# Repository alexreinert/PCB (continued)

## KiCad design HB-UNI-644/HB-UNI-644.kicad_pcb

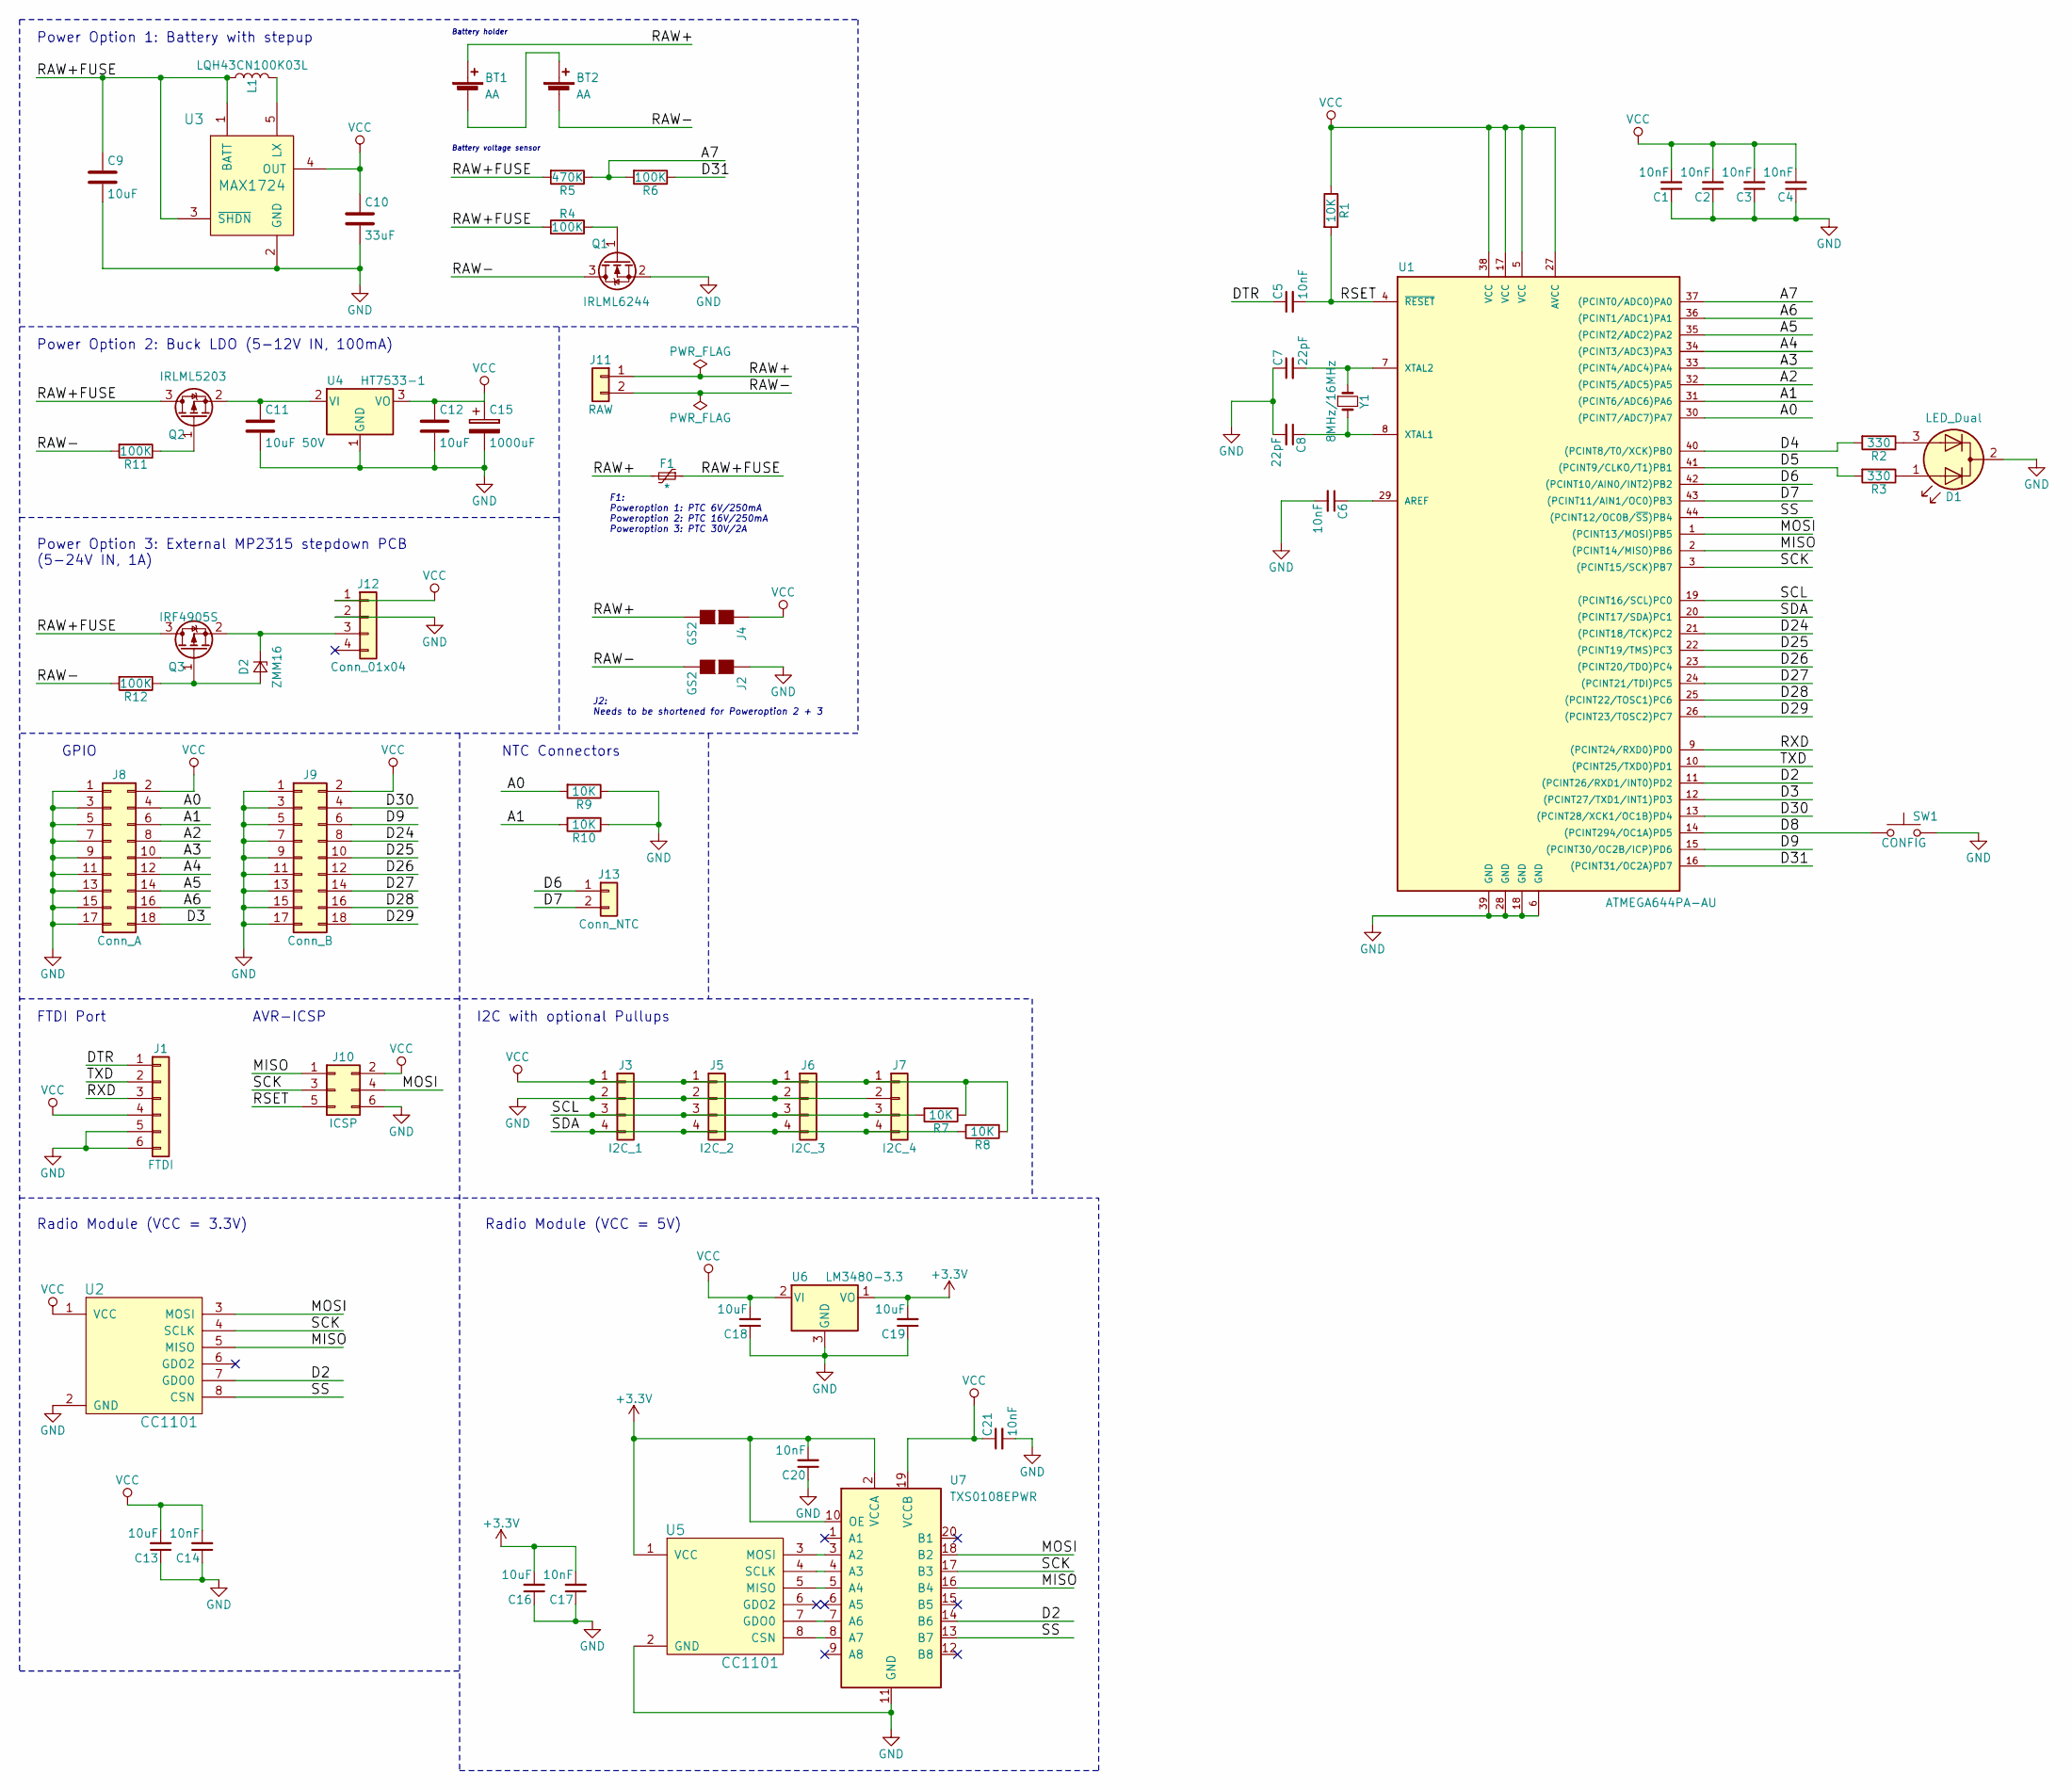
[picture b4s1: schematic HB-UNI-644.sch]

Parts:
BT1, BT2: AA; BATTERY_HOLDER_GOOBAY_AA
C1, C2, C3, C4, C5, C6, C14, C17, C20, C21: 10nF; C_0805_HandSoldering
C7, C8: 22pF; C_0805_HandSoldering
C9, C12, C13, C16, C18, C19: 10uF; C_0805_HandSoldering
C10: 33uF; C_1206_HandSoldering
C11: 10uF 50V; C_1206_HandSoldering
C15: 1000uF; CP_Radial_D8.0mm_P3.50mm
D1: LED_Dual; LED_D3.0mm-3
D2: ZMM16; D_MiniMELF_Handsoldering
F1: *; R_1206_HandSoldering
J1: FTDI; Pin_Header_Straight_1x06_Pitch2.54mm
J2, J4: GS2
J3: I2C_1; Pin_Header_Straight_1x04_Pitch2.54mm
J5: I2C_2; Pin_Header_Straight_1x04_Pitch2.54mm
J6: I2C_3; Pin_Header_Straight_1x04_Pitch2.54mm
J7: I2C_4; Pin_Header_Straight_1x04_Pitch2.54mm
J8: Conn_A; Pin_Header_Straight_2x09_Pitch2.54mm
J9: Conn_B; Pin_Header_Straight_2x09_Pitch2.54mm
J10: ICSP; Pin_Header_Straight_2x03_Pitch2.54mm
J11: RAW; Pin_Header_Straight_1x02_Pitch2.54mm
J12: Conn_01x04; Pin_Header_Straight_1x04_Pitch2.54mm
J13: Conn_NTC; Pin_Header_Straight_2x01_Pitch2.54mm
L1: LQH43CN100K03L; L_1812_HandSoldering
Q1: IRLML6244; SOT-23_Handsoldering
Q2: IRLML5203; SOT-23_Handsoldering
Q3: IRF4905S; TO-263-2
R1, R7, R8, R9, R10: 10K; R_0805_HandSoldering
R2, R3: 330; R_0805_HandSoldering
R4, R6, R11, R12: 100K; R_0805_HandSoldering
R5: 470K; R_0805_HandSoldering
SW1: CONFIG; SW_SPST_FSMSM
U1: ATMEGA644PA-AU; TQFP-44_10x10mm_Pitch0.8mm
U2, U5: CC1101
U3: MAX1724; TSOT-23-5_HandSoldering
U4: HT7533-1; SOT-89-3_Handsoldering
U6: LM3480-3.3; SOT-23
U7: TXS0108EPWR; TSSOP-20_4.4x6.5mm_Pitch0.65mm
Y1: 8MHz/16MHz; Crystal_HC49-U_Vertical

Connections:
+3V3: C16.2, C17.2, C19.2, C20.2, U5.1 (VCC), U6.1 (VO), U7.2 (VCCA), U7.10 (OE)
/A0: J8.4, R9.2, U1.30 ((PCINT7/ADC7)PA7)
/A1: J8.6, R10.2, U1.31 ((PCINT6/ADC6)PA6)
/A2: J8.8, U1.32 ((PCINT5/ADC5)PA5)
/A3: J8.10, U1.33 ((PCINT4/ADC4)PA4)
/A4: J8.12, U1.34 ((PCINT3/ADC3)PA3)
/A5: J8.14, U1.35 ((PCINT2/ADC2)PA2)
/A6: J8.16, U1.36 ((PCINT1/ADC1)PA1)
/A7: R5.1, R6.2, U1.37 ((PCINT0/ADC0)PA0)
/D2: U1.11 ((PCINT26/RXD1/INT0)PD2), U2.7 (GDO0), U7.14 (B6)
/D3: J8.18, U1.12 ((PCINT27/TXD1/INT1)PD3)
/D4: R2.2, U1.40 ((PCINT8/T0/XCK)PB0)
/D5: R3.2, U1.41 ((PCINT9/CLKO/T1)PB1)
/D6: J13.1, U1.42 ((PCINT10/AIN0/INT2)PB2)
/D7: J13.2, U1.43 ((PCINT11/AIN1/OC0)PB3)
/D8: SW1.1, U1.14 ((PCINT294/OC1A)PD5)
/D9: J9.6, U1.15 ((PCINT30/OC2B/ICP)PD6)
/D24: J9.8, U1.21 ((PCINT18/TCK)PC2)
/D25: J9.10, U1.22 ((PCINT19/TMS)PC3)
/D26: J9.12, U1.23 ((PCINT20/TDO)PC4)
/D27: J9.14, U1.24 ((PCINT21/TDI)PC5)
/D28: J9.16, U1.25 ((PCINT22/TOSC1)PC6)
/D29: J9.18, U1.26 ((PCINT23/TOSC2)PC7)
/D30: J9.4, U1.13 ((PCINT28/XCK1/OC1B)PD4)
/D31: R6.1, U1.16 ((PCINT31/OC2A)PD7)
/DTR: C5.1, J1.1
/MISO: J10.1, U1.2 ((PCINT14/MISO)PB6), U2.5 (MISO), U7.16 (B4)
/MOSI: J10.4, U1.1 ((PCINT13/MOSI)PB5), U2.3 (MOSI), U7.18 (B2)
/RAW+: BT1.1 (+), F1.2, J4.2 (G2), J11.1
/RAW+FUSE: C9.1, F1.1, L1.1, Q2.3 (D), Q3.3 (D), R4.2, R5.2, U3.1 (BATT), U3.3 (~SHDN)
/RAW-: BT2.2 (-), J2.2 (G2), J11.2, Q1.3 (D), R11.2, R12.2
/RSET: C5.2, J10.5, R1.2, U1.4 (~RESET)
/RXD: J1.3, U1.9 ((PCINT24/RXD0)PD0)
/SCK: J10.3, U1.3 ((PCINT15/SCK)PB7), U2.4 (SCLK), U7.17 (B3)
/SCL: J3.3, J5.3, J6.3, J7.3, R7.2, U1.19 ((PCINT16/SCL)PC0)
/SDA: J3.4, J5.4, J6.4, J7.4, R8.2, U1.20 ((PCINT17/SDA)PC1)
/SS: U1.44 ((PCINT12/OC0B/~SS~)PB4), U2.8 (CSN), U7.13 (B7)
/TXD: J1.2, U1.10 ((PCINT25/TXD0)PD1)
GND: C1.1, C2.1, C3.1, C4.1, C6.2, C7.1, C8.2, C9.2, C10.2, C11.2, C12.2, C13.1, C14.1, C15.2, C16.1, C17.1, C18.1, C19.1, C20.1, C21.2, D1.2 (K), J1.5, J1.6, J2.1 (G1), J3.2, J5.2, J6.2, J7.2, J8.1, J8.3, J8.5, J8.7, J8.9, J8.11, J8.13, J8.15, J8.17, J9.1, J9.3, J9.5, J9.7, J9.9, J9.11, J9.13, J9.15, J9.17, J10.6, J12.2, Q1.2 (S), R9.1, R10.1, SW1.2, U1.6 (GND), U1.18 (GND), U1.28 (GND), U1.39 (GND), U2.2 (GND), U3.2 (GND), U4.1 (GND), U5.2 (GND), U6.3 (GND), U7.11 (GND)
unnamed: BT1.2 (-), BT2.1 (+)
unnamed: C6.1, U1.29 (AREF)
unnamed: C7.2, U1.7 (XTAL2), Y1.1
unnamed: C8.1, U1.8 (XTAL1), Y1.2
unnamed: C11.1, Q2.2 (S), U4.2 (VI)
unnamed: D1.1 (A1), R3.1
unnamed: D1.3 (A2), R2.1
unnamed: D2.1 (K), J12.3, Q3.2 (S)
unnamed: D2.2 (A), Q3.1 (G), R12.1
unnamed: L1.2, U3.5 (LX)
unnamed: Q1.1 (G), R4.1
unnamed: Q2.1 (G), R11.1
unnamed: U5.3 (MOSI), U7.3 (A2)
unnamed: U5.4 (SCLK), U7.4 (A3)
unnamed: U5.5 (MISO), U7.5 (A4)
unnamed: U5.7 (GDO0), U7.7 (A6)
unnamed: U5.8 (CSN), U7.8 (A7)
VCC: C1.2, C2.2, C3.2, C4.2, C10.1, C12.1, C13.2, C14.2, C15.1, C18.2, C21.1, J1.4, J3.1, J4.1 (G1), J5.1, J6.1, J7.1, J8.2, J9.2, J10.2, J12.1, R1.1, R7.1, R8.1, U1.5 (VCC), U1.17 (VCC), U1.27 (AVCC), U1.38 (VCC), U2.1 (VCC), U3.4 (OUT), U4.3 (VO), U6.2 (VI), U7.19 (VCCB)

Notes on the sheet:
I2C with optional Pullups
AVR-ICSP
FTDI Port
GPIO
NTC Connectors
Power Option 1: Battery with stepup
Power Option 2: Buck LDO (5-12V IN, 100mA)
Battery holder
Battery voltage sensor
Power Option 3: External MP2315 stepdown PCB (5-24V IN, 1A)
F1: Poweroption 1: PTC 6V/250mA Poweroption 2: PTC 16V/250mA Poweroption 3: PTC 30V/2A
J2: Needs to be shortened for Poweroption 2 + 3
Radio Module (VCC = 3.3V)
Radio Module (VCC = 5V)

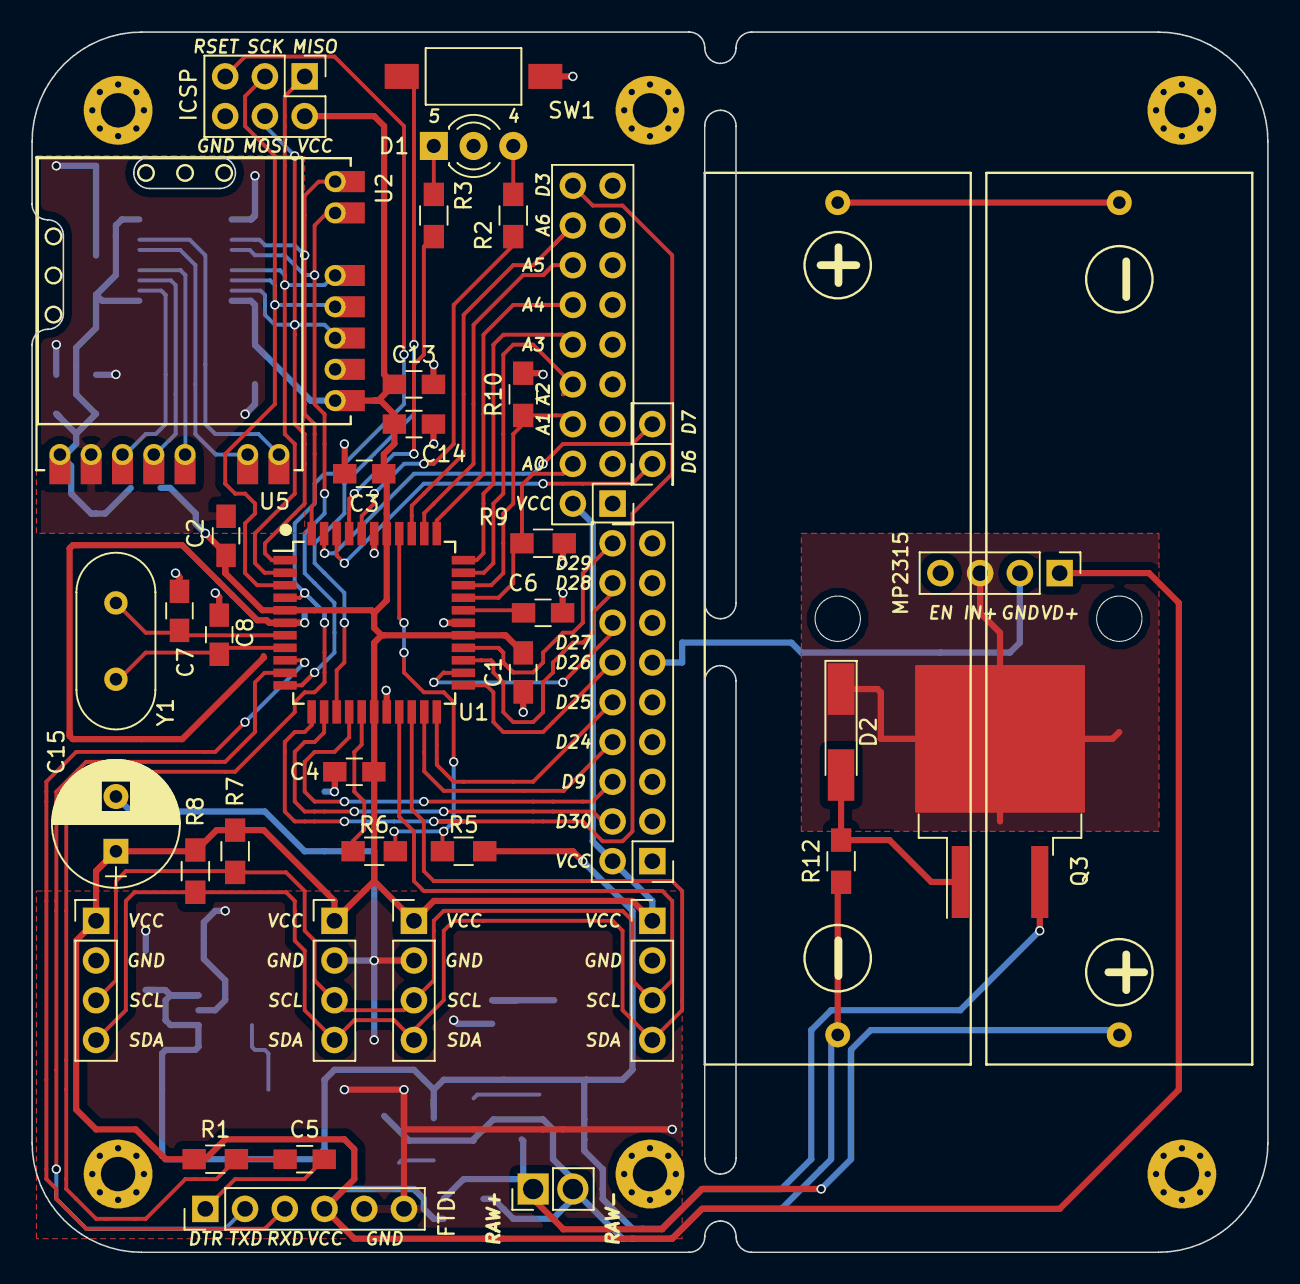
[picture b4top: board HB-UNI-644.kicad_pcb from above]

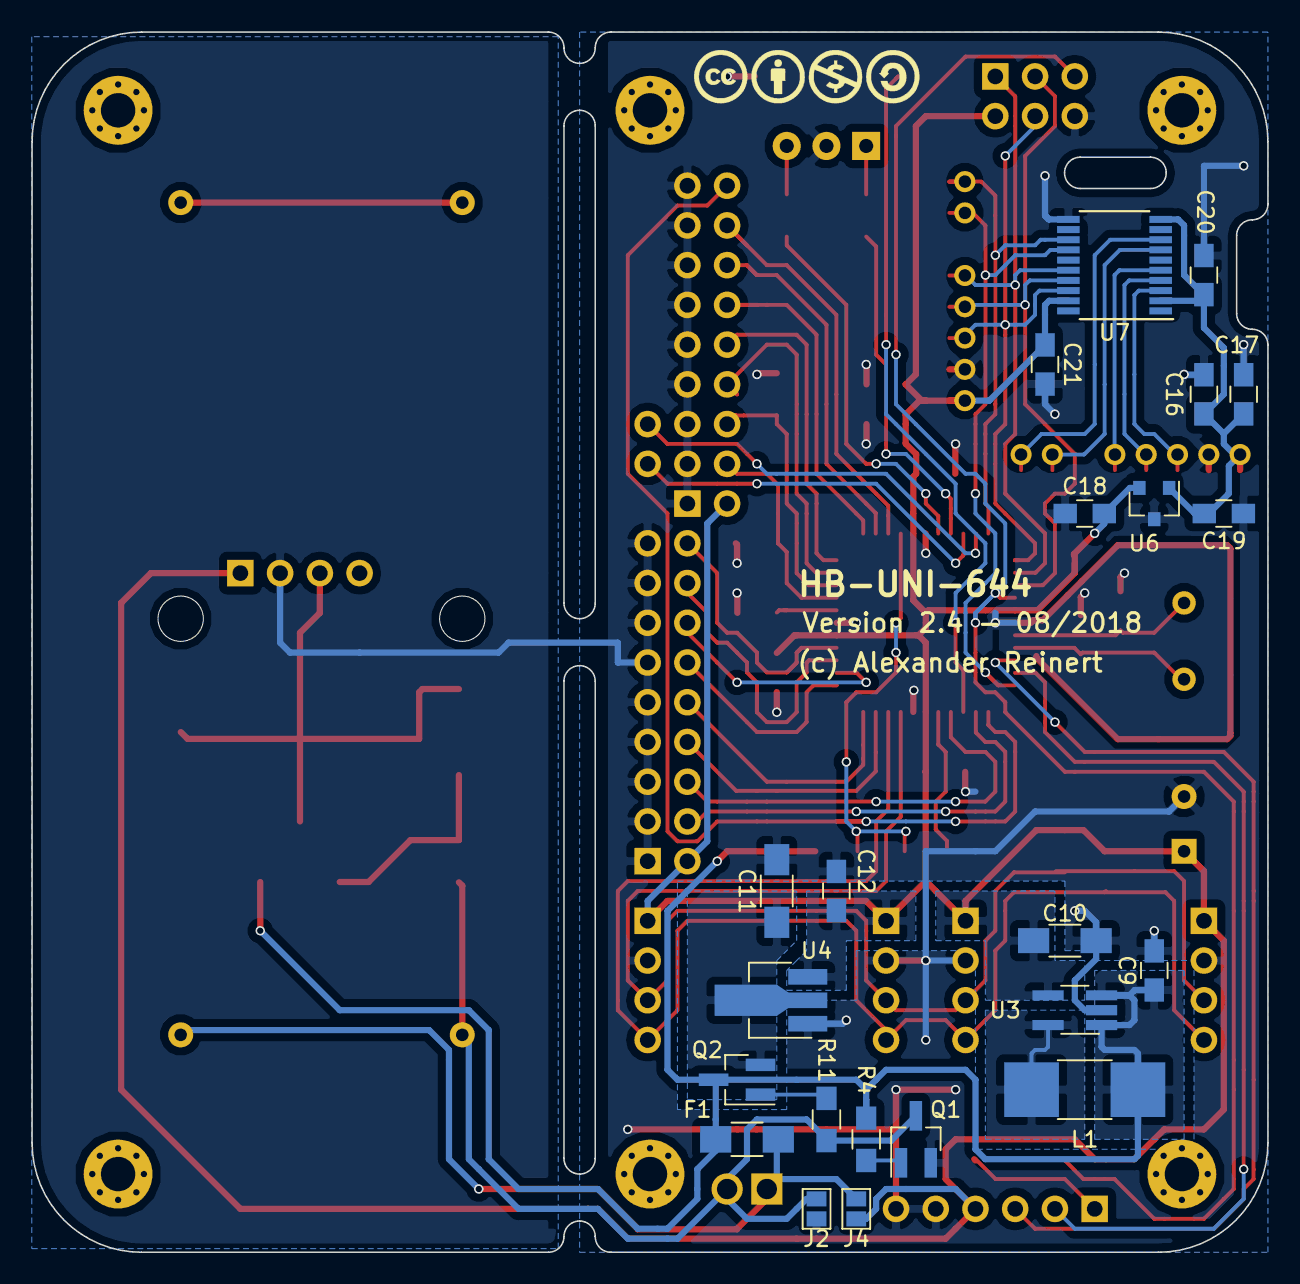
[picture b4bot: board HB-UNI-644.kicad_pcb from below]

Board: 2 copper layers, 79.0 x 78.0 mm, 64 parts (22 on the bottom side), 57 nets.

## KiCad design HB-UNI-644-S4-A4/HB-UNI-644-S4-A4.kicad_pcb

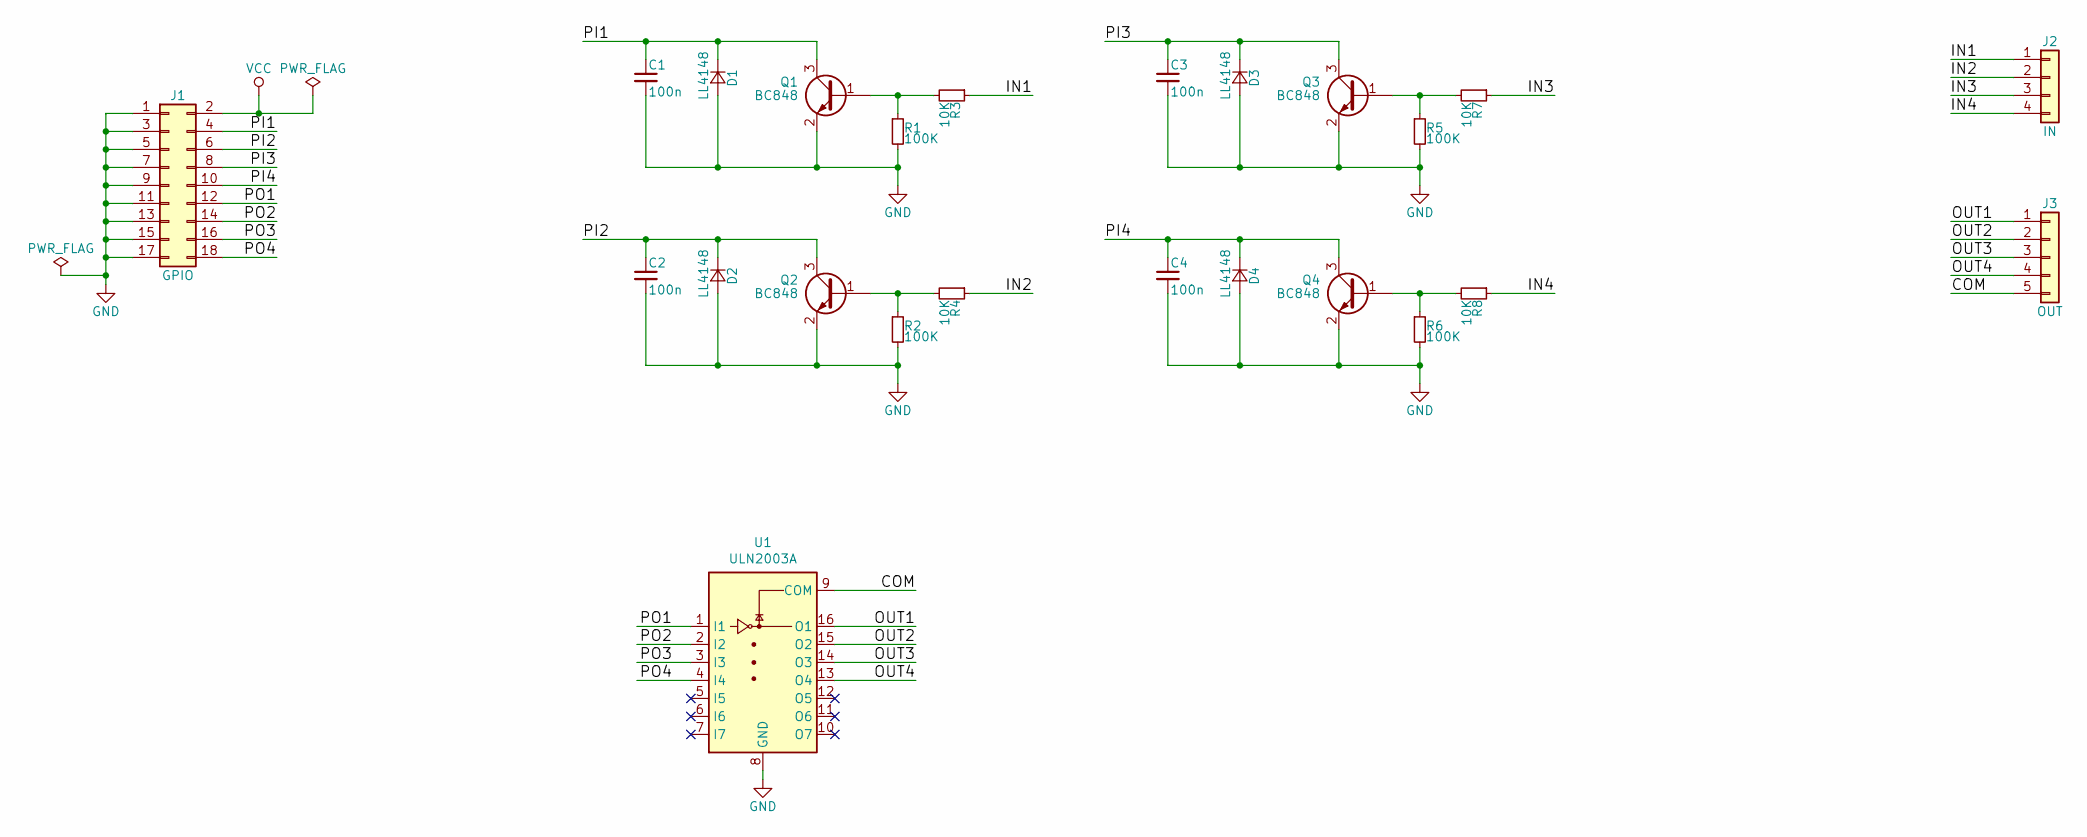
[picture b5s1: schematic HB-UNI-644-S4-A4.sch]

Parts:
C1, C2, C3, C4: 100n; C_0805_HandSoldering
D1, D2, D3, D4: LL4148; D_MiniMELF
J1: GPIO; Pin_Header_Straight_2x09_Pitch2.54mm
J2: IN; Molex_SPOX-5267_22-03-5045_04x2.54mm_Straight
J3: OUT; Molex_SPOX-5267_22-03-5055_05x2.54mm_Straight
Q1, Q2, Q3, Q4: BC848; SOT-23
R1, R2, R5, R6: 100K; R_0805_HandSoldering
R3, R4, R7, R8: 10K; R_0805_HandSoldering
U1: ULN2003A; SOIC-16_3.9x9.9mm_Pitch1.27mm

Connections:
/COM: J3.5, U1.9 (COM)
/IN1: J2.1, R3.1
/IN2: J2.2, R4.1
/IN3: J2.3, R7.1
/IN4: J2.4, R8.1
/OUT1: J3.1, U1.16 (O1)
/OUT2: J3.2, U1.15 (O2)
/OUT3: J3.3, U1.14 (O3)
/OUT4: J3.4, U1.13 (O4)
/PI1: C1.1, D1.1 (K), J1.4, Q1.3 (C)
/PI2: C2.1, D2.1 (K), J1.6, Q2.3 (C)
/PI3: C3.1, D3.1 (K), J1.8, Q3.3 (C)
/PI4: C4.1, D4.1 (K), J1.10, Q4.3 (C)
/PO1: J1.12, U1.1 (I1)
/PO2: J1.14, U1.2 (I2)
/PO3: J1.16, U1.3 (I3)
/PO4: J1.18, U1.4 (I4)
GND: C1.2, C2.2, C3.2, C4.2, D1.2 (A), D2.2 (A), D3.2 (A), D4.2 (A), J1.1, J1.3, J1.5, J1.7, J1.9, J1.11, J1.13, J1.15, J1.17, Q1.2 (E), Q2.2 (E), Q3.2 (E), Q4.2 (E), R1.2, R2.2, R5.2, R6.2, U1.8 (GND)
unnamed: Q1.1 (B), R1.1, R3.2
unnamed: Q2.1 (B), R2.1, R4.2
unnamed: Q3.1 (B), R5.1, R7.2
unnamed: Q4.1 (B), R6.1, R8.2
VCC: J1.2

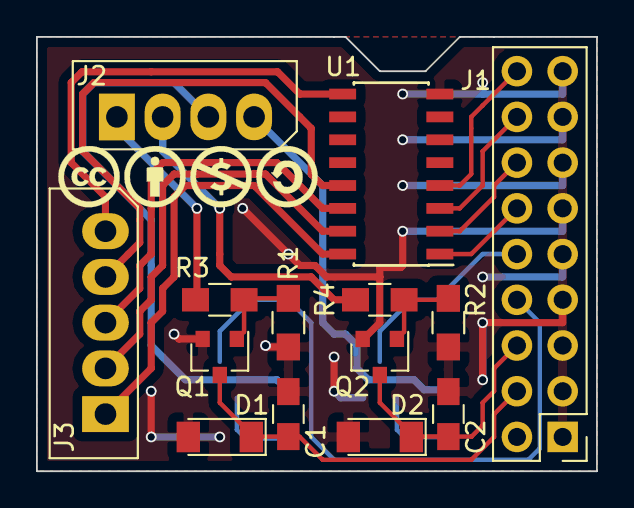
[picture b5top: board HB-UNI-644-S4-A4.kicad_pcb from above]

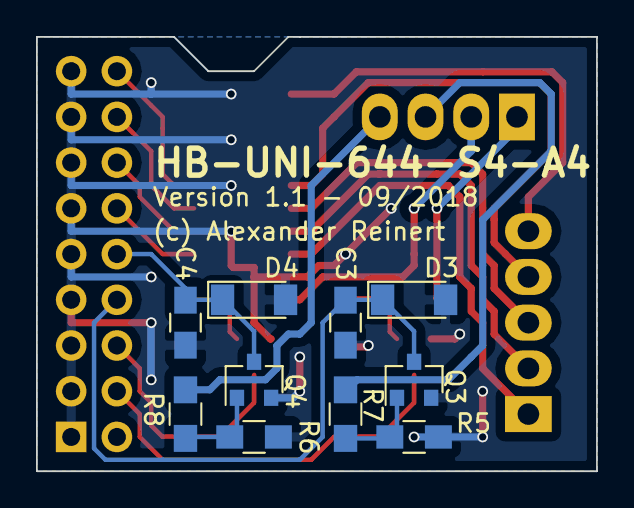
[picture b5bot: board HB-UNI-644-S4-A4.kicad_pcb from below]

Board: 2 copper layers, 31.1 x 24.1 mm, 24 parts (10 on the bottom side), 22 nets.

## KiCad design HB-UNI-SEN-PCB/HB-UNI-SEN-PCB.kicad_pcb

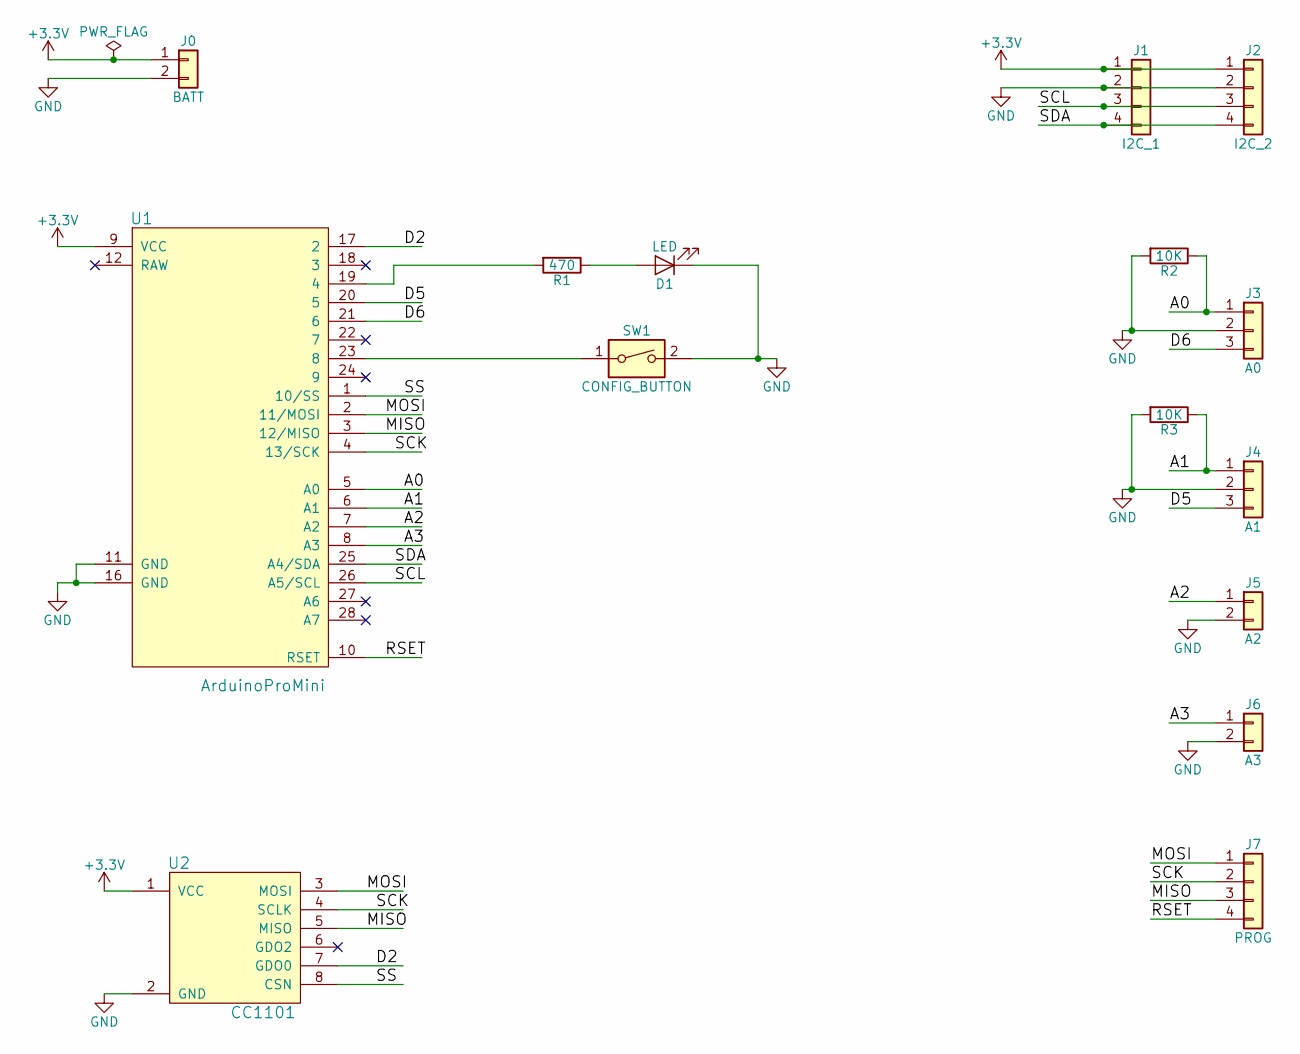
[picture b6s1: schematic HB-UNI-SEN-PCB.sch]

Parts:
D1: LED; LED_D3.0mm
J0: BATT; Pin_Header_Straight_1x02_Pitch2.54mm
J1: I2C_1; Pin_Header_Straight_1x04_Pitch2.54mm
J2: I2C_2; Pin_Header_Straight_1x04_Pitch2.54mm
J3: A0; Pin_Header_Straight_1x03_Pitch2.54mm
J4: A1; Pin_Header_Straight_1x03_Pitch2.54mm
J5: A2; Pin_Header_Straight_1x02_Pitch2.54mm
J6: A3; Pin_Header_Straight_1x02_Pitch2.54mm
J7: PROG; Pin_Header_Straight_1x04_Pitch2.54mm
R1: 470; R_Axial_DIN0207_L6.3mm_D2.5mm_P10.16mm_Horizontal
R2, R3: 10K; R_Axial_DIN0207_L6.3mm_D2.5mm_P10.16mm_Horizontal
SW1: CONFIG_BUTTON; SW_PUSH_6mm_h5mm
U1: ArduinoProMini
U2: CC1101

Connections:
+3V3: J0.1, J1.1, J2.1, U1.9 (VCC), U2.1 (VCC)
/A0: J3.1, R2.1, U1.5 (A0)
/A1: J4.1, R3.1, U1.6 (A1)
/A2: J5.1, U1.7 (A2)
/A3: J6.1, U1.8 (A3)
/D2: U1.17 (2), U2.7 (GDO0)
/D5: J4.3, U1.20 (5)
/D6: J3.3, U1.21 (6)
/MISO: J7.3, U1.3 (12/MISO), U2.5 (MISO)
/MOSI: J7.1, U1.2 (11/MOSI), U2.3 (MOSI)
/RSET: J7.4, U1.10 (RSET)
/SCK: J7.2, U1.4 (13/SCK), U2.4 (SCLK)
/SCL: J1.3, J2.3, U1.26 (A5/SCL)
/SDA: J1.4, J2.4, U1.25 (A4/SDA)
/SS: U1.1 (10/SS), U2.8 (CSN)
GND: D1.1 (K), J0.2, J1.2, J2.2, J3.2, J4.2, J5.2, J6.2, R2.2, R3.2, SW1.2, U1.11 (GND), U1.16 (GND), U2.2 (GND)
unnamed: D1.2 (A), R1.1
unnamed: R1.2, U1.19 (4)
unnamed: SW1.1, U1.23 (8)

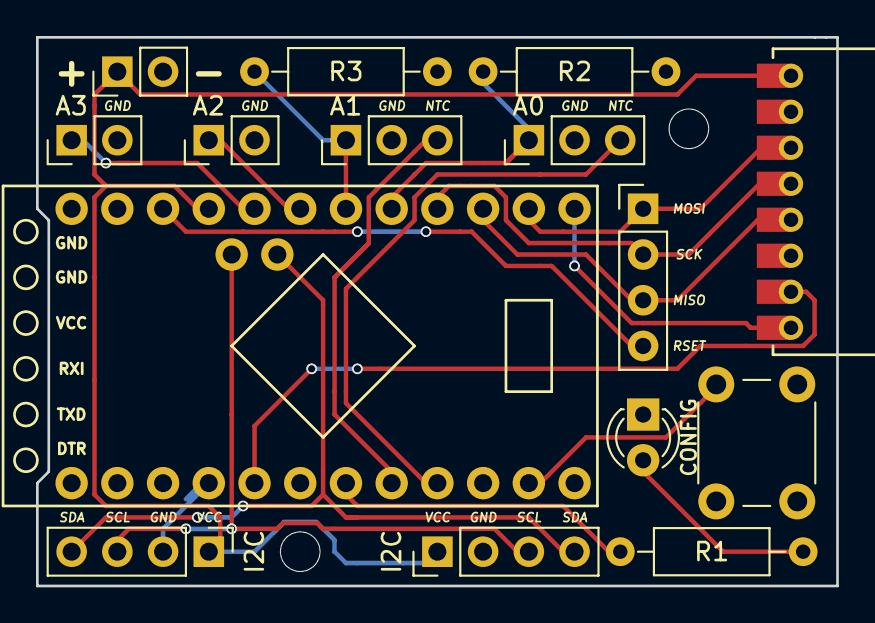
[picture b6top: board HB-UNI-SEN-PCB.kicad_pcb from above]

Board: 2 copper layers, 44.4 x 30.5 mm, 15 parts (0 on the bottom side), 19 nets.

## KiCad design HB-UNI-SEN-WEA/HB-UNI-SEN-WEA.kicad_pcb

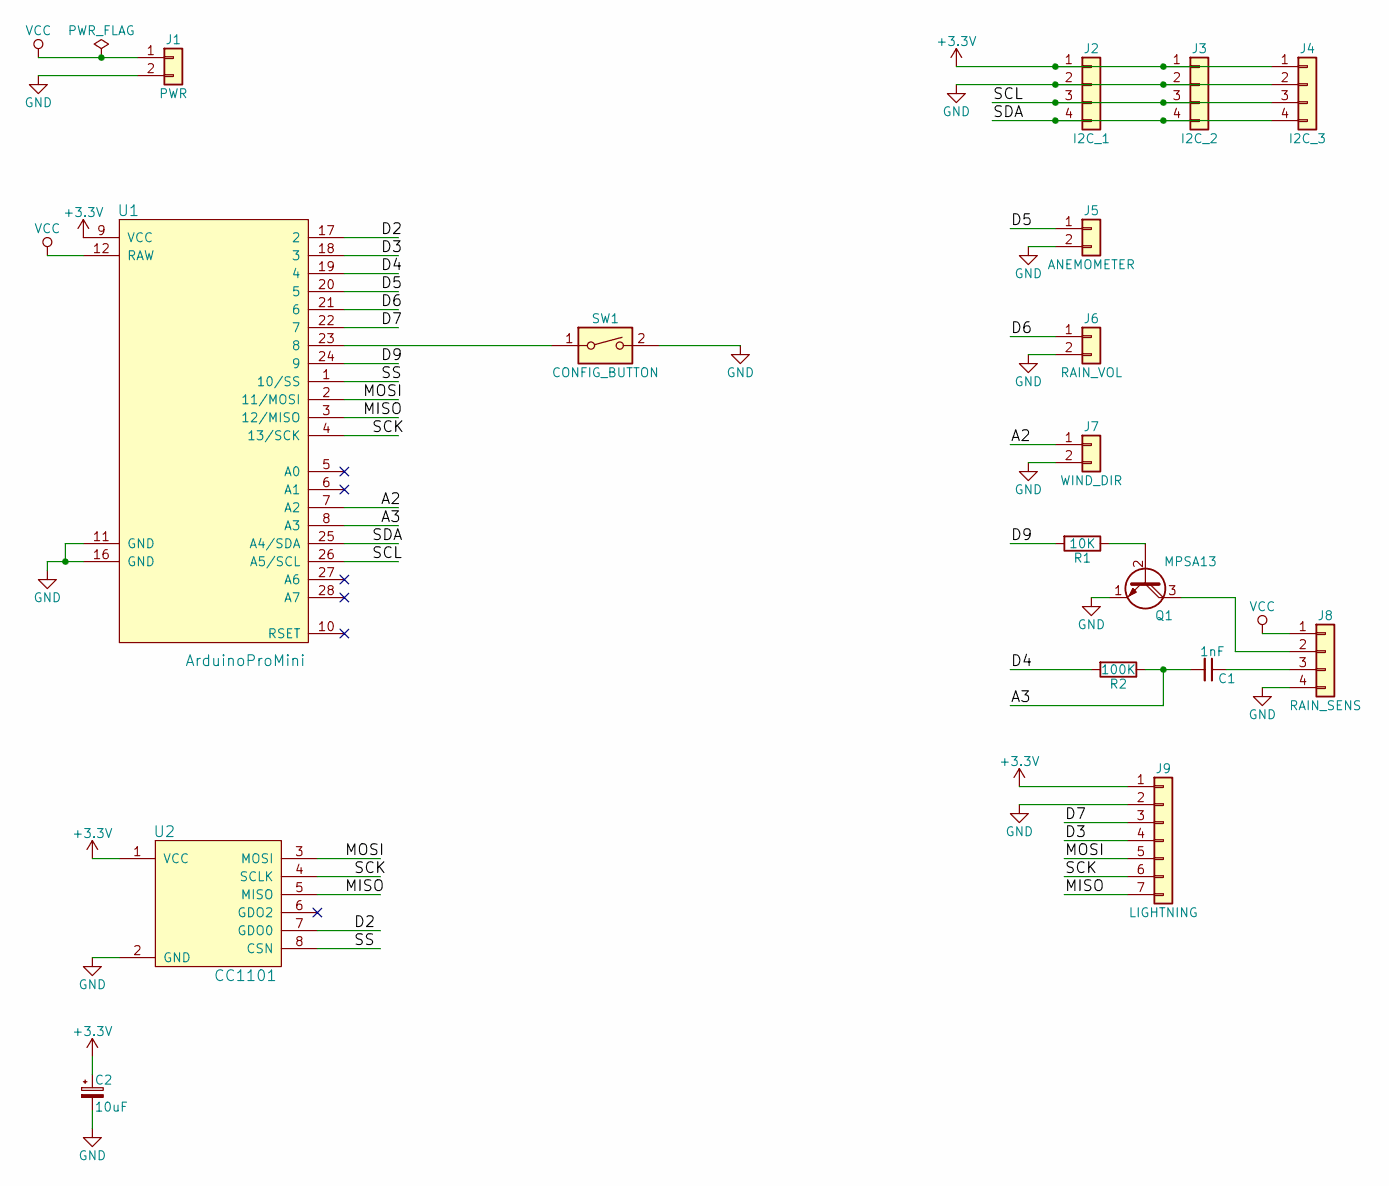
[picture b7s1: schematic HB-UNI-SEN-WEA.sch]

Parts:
C1: 1nF; C_Disc_D3.8mm_W2.6mm_P2.50mm
C2: 10uF; CP_Radial_D4.0mm_P1.50mm
J1: PWR; Molex_SPOX-5267_22-03-5025_02x2.54mm_Straight
J2: I2C_1; Molex_SPOX-5267_22-03-5045_04x2.54mm_Straight
J3: I2C_2; Molex_SPOX-5267_22-03-5045_04x2.54mm_Straight
J4: I2C_3; Molex_SPOX-5267_22-03-5045_04x2.54mm_Straight
J5: ANEMOMETER; Molex_SPOX-5267_22-03-5025_02x2.54mm_Straight
J6: RAIN_VOL; Molex_SPOX-5267_22-03-5025_02x2.54mm_Straight
J7: WIND_DIR; Molex_SPOX-5267_22-03-5025_02x2.54mm_Straight
J8: RAIN_SENS; Molex_SPOX-5267_22-03-5045_04x2.54mm_Straight
J9: LIGHTNING; Molex_SPOX-5267_22-03-5075_07x2.54mm_Straight
Q1: MPSA13; TO-92_Inline_Narrow_Oval
R1: 10K; R_Axial_DIN0207_L6.3mm_D2.5mm_P10.16mm_Horizontal
R2: 100K; R_Axial_DIN0207_L6.3mm_D2.5mm_P10.16mm_Horizontal
SW1: CONFIG_BUTTON; SW_PUSH_6mm_h5mm
U1: ArduinoProMini
U2: CC1101

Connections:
+3V3: C2.1, J2.1, J3.1, J4.1, J9.1, U1.9 (VCC), U2.1 (VCC)
/A2: J7.1, U1.7 (A2)
/A3: C1.2, R2.1, U1.8 (A3)
/D2: U1.17 (2), U2.7 (GDO0)
/D3: J9.4, U1.18 (3)
/D4: R2.2, U1.19 (4)
/D5: J5.1, U1.20 (5)
/D6: J6.1, U1.21 (6)
/D7: J9.3, U1.22 (7)
/D9: R1.2, U1.24 (9)
/MISO: J9.7, U1.3 (12/MISO), U2.5 (MISO)
/MOSI: J9.5, U1.2 (11/MOSI), U2.3 (MOSI)
/SCK: J9.6, U1.4 (13/SCK), U2.4 (SCLK)
/SCL: J2.3, J3.3, J4.3, U1.26 (A5/SCL)
/SDA: J2.4, J3.4, J4.4, U1.25 (A4/SDA)
/SS: U1.1 (10/SS), U2.8 (CSN)
GND: C2.2, J1.2, J2.2, J3.2, J4.2, J5.2, J6.2, J7.2, J8.4, J9.2, Q1.1 (E), SW1.2, U1.11 (GND), U1.16 (GND), U2.2 (GND)
unnamed: C1.1, J8.3
unnamed: J8.2, Q1.3 (C)
unnamed: Q1.2 (B), R1.1
unnamed: SW1.1, U1.23 (8)
VCC: J1.1, J8.1, U1.12 (RAW)

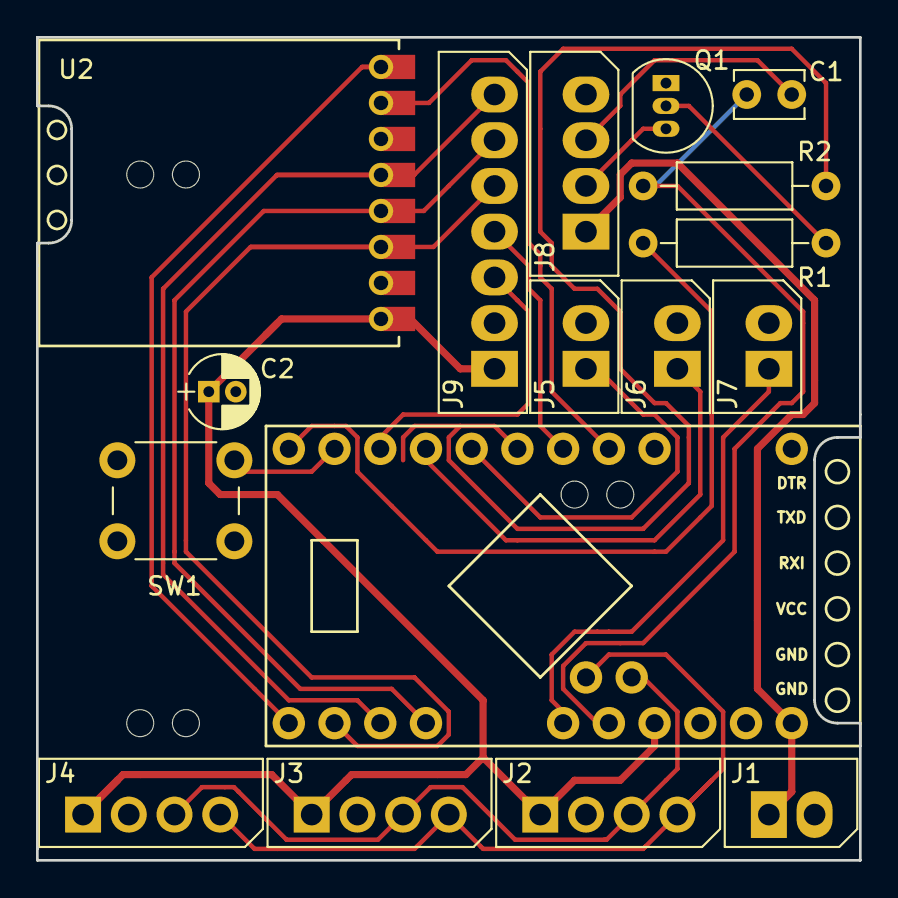
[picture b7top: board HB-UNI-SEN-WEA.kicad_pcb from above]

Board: 2 copper layers, 45.7 x 45.7 mm, 17 parts (0 on the bottom side), 22 nets.

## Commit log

2018-04-24 Added Schematic PDF and PCB images
2018-04-25 Optimized footprints
2018-04-26 Added Readme
2018-05-03 Added reverse polarity protection
2018-05-03 Added HB-UNI-SEN-O
2018-05-08 Optimized drill hole size for IRLU024N
2018-06-16 Added new PCB HB-UNI-644, removed unfinished HB-UNI-SEN-O
2018-06-17 Added hint to schematic which mosfet to use on HB-UNI-644
2018-06-17 Removed invalid file
2018-07-29 Revision 2 of HB-UNI-644
2018-07-30 Fixed Gerber files of HB-UNI-SEN-BATT (fixes #2)
    Fixed README of HB-UNI-BATT (fixes #1)
    Optimized Silkscreen of HB-UNI-644
2018-07-31 Fixed Stepdown module on HB-UNI-644
2018-08-01 Relicened under CC BY-NC-SA 4.0
2018-08-02 Relicened under CC BY-ND-SA
2018-08-08 Added HB-UNI-SEN-WEA
2018-08-08 Fixed README
2018-08-16 Fixed Silkscreen of D6 and D7 on HB-UNI-644
2018-10-26 * Switched to Kicad 5 * Added HB-UNI-644-S4-A4 addon Board
2021-07-29 Added HB-RF-USB
2021-07-29 - Update to Kicad 5 symbol and footprint libs
    - Use different Micro USB Connector for better mechanical stability
2021-07-29 Added HB-RF-USB-2
2021-07-29 Added HB-RF-ETH
